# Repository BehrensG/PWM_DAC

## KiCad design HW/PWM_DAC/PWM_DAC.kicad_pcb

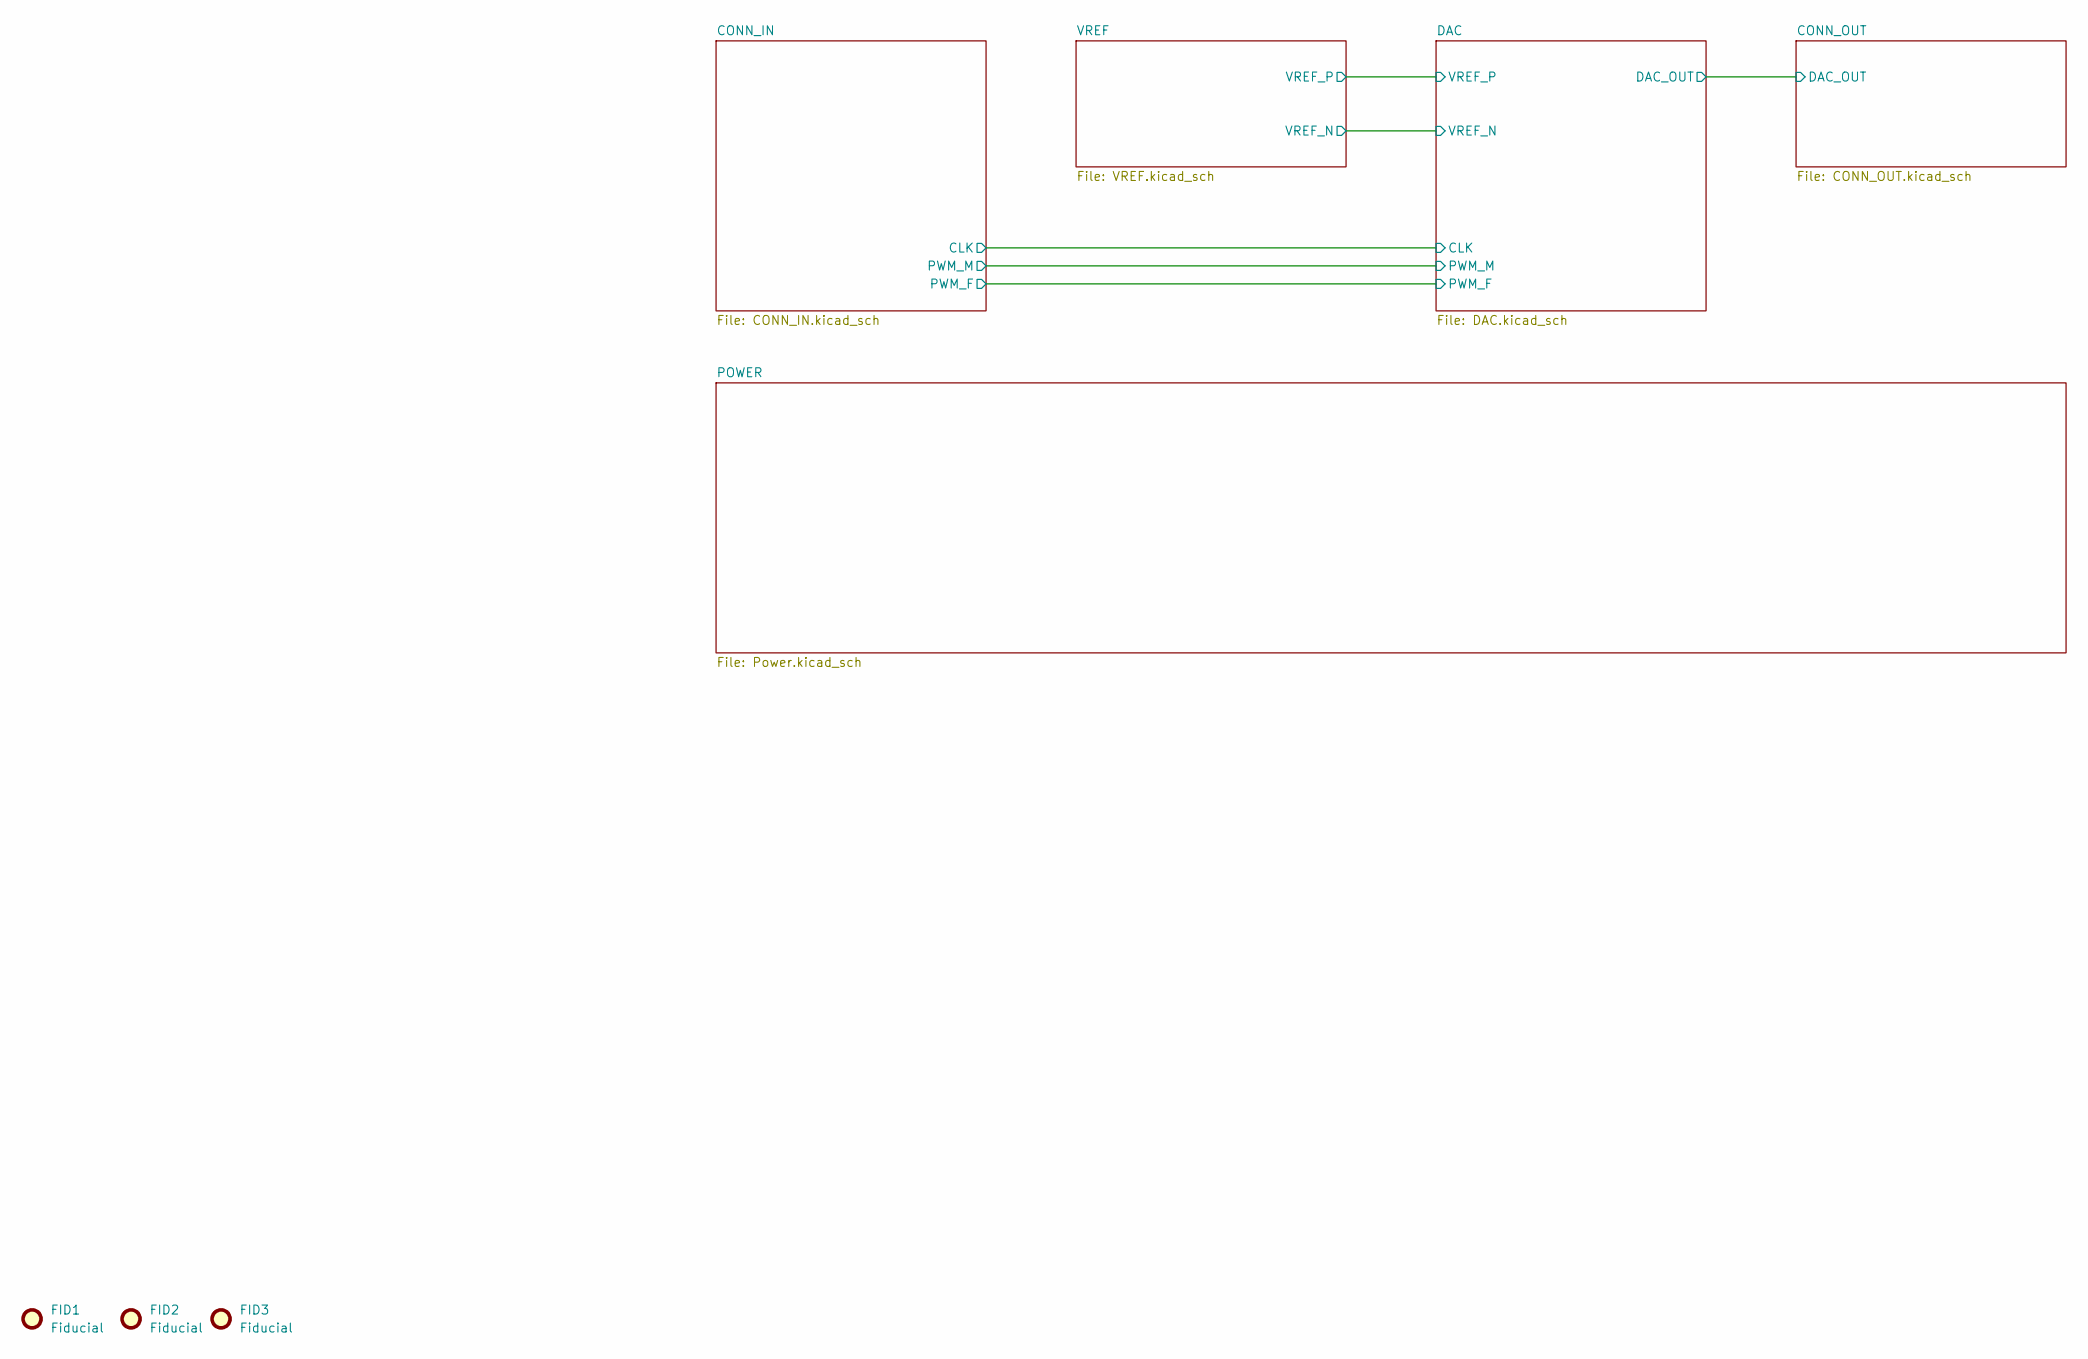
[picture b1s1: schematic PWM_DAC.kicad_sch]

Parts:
FID1, FID2, FID3: Fiducial; Fiducial_1.5mm_Mask3mm

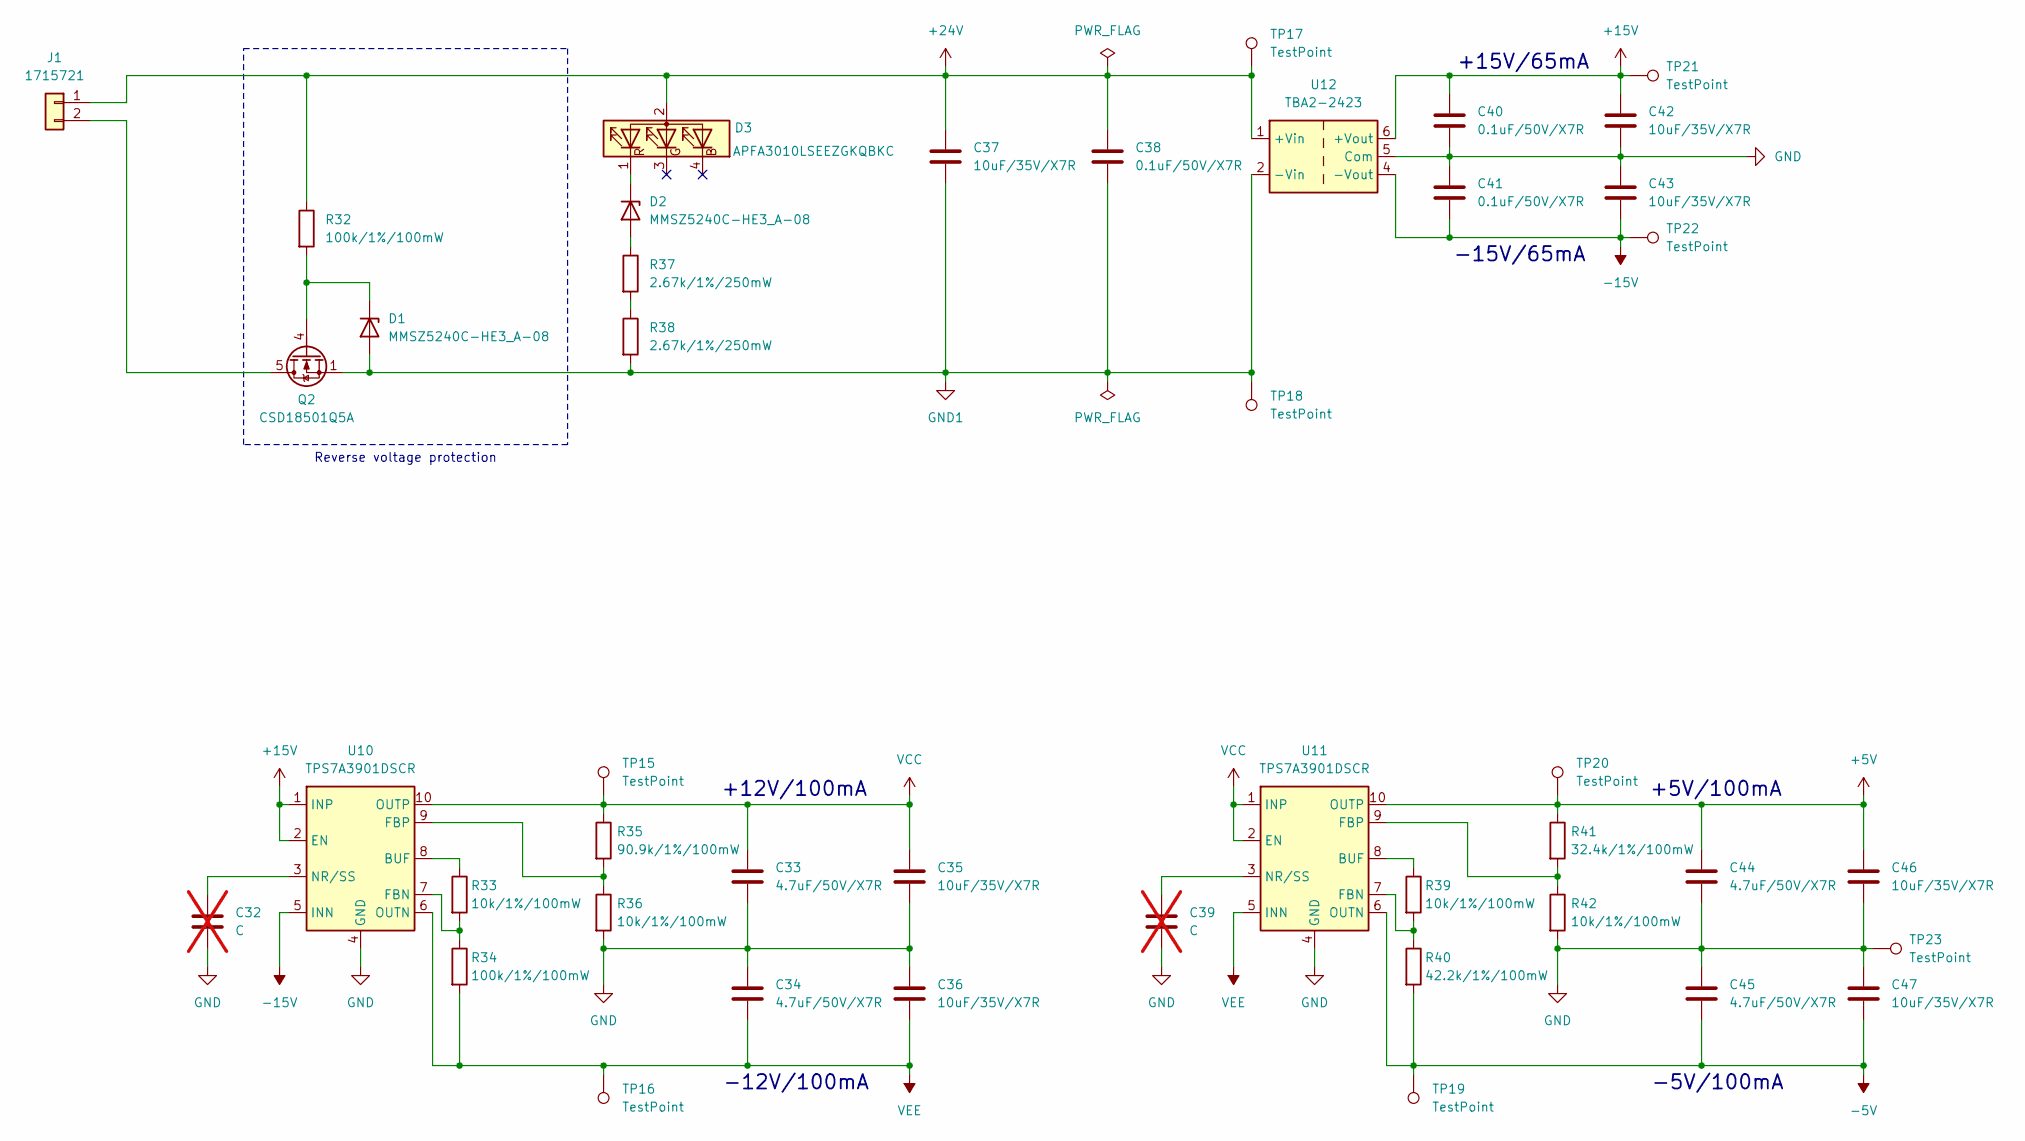
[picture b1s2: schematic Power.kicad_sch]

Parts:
C32, C39: C; C_0603_1608Metric_Pad1.08x0.95mm_HandSolder; not fitted
C33, C34, C44, C45: 4.7uF/50V/X7R; C_1206_3216Metric_Pad1.33x1.80mm_HandSolder
C35, C36, C37, C42, C43, C46, C47: 10uF/35V/X7R; C_1206_3216Metric_Pad1.33x1.80mm_HandSolder
C38, C40, C41: 0.1uF/50V/X7R; C_0603_1608Metric_Pad1.08x0.95mm_HandSolder
D1, D2: MMSZ5240C-HE3_A-08; D_SOD-123
D3: APFA3010LSEEZGKQBKC; LED_Kingbright_APFA3010_3x1.5mm_Horizontal
J1: 1715721; TerminalBlock_Phoenix_MKDS-1,5-2_1x02_P5.00mm_Horizontal
Q2: CSD18501Q5A; TDSON-8-1
R32, R34: 100k/1%/100mW; R_0603_1608Metric_Pad0.98x0.95mm_HandSolder
R33, R36, R39, R42: 10k/1%/100mW; R_0603_1608Metric_Pad0.98x0.95mm_HandSolder
R35: 90.9k/1%/100mW; R_0603_1608Metric_Pad0.98x0.95mm_HandSolder
R37, R38: 2.67k/1%/250mW; R_0805_2012Metric_Pad1.20x1.40mm_HandSolder
R40: 42.2k/1%/100mW; R_0603_1608Metric_Pad0.98x0.95mm_HandSolder
R41: 32.4k/1%/100mW; R_0603_1608Metric_Pad0.98x0.95mm_HandSolder
TP15, TP16, TP17, TP18, TP19, TP20, TP21, TP22, TP23: TestPoint; TestPoint_Pad_D1.5mm
U10, U11: TPS7A3901DSCR; Texas_S-PVSON-N10_ThermalVias
U12: TBA2-2423; Converter_DCDC_TRACO_TBA2-xxxx_Dual_THT

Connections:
+5V: C44.1, C46.1, R41.1, TP20.1 (1_1), U11.10 (OUTP); also elsewhere on the board
+15V: C40.2, C42.2, TP21.1 (1_1), U10.1 (INP), U10.2 (EN), U12.6 (+Vout)
+24V: C37.2, C38.2, D3.2 (A), J1.1, R32.1, TP17.1 (1_1), U12.1 (+Vin)
-5V: C45.2, C47.2, R40.2, TP19.1 (1_1), U11.6 (OUTN); also elsewhere on the board
-15V: C41.1, C43.1, TP22.1 (1_1), U10.5 (INN), U12.4 (-Vout)
GND: C32.2, C33.2, C34.1, C35.2, C36.1, C39.2, C40.1, C41.2, C42.1, C43.2, C44.2, C45.1, C46.2, C47.1, R36.2, R42.2, TP23.1 (1_1), U10.4 (GND), U10.11 (GND), U11.4 (GND), U11.11 (GND), U12.5 (Com); also elsewhere on the board
GND1: C37.1, C38.1, D1.2 (A), Q2.1 (S), Q2.2 (S), Q2.3 (S), R38.2, TP18.1 (1_1), U12.2 (-Vin)
unnamed: D1.1 (K), Q2.4 (G), R32.2
unnamed: D2.2 (A), R37.1
unnamed: D2.1 (K), D3.1 (R)
unnamed: J1.2, Q2.5 (D)
unnamed: R37.2, R38.1
unnamed: R33.1, U10.8 (BUF)
unnamed: R33.2, R34.1, U10.7 (FBN)
unnamed: R35.2, R36.1, U10.9 (FBP)
unnamed: C32.1, U10.3 (NR/SS)
unnamed: R39.1, U11.8 (BUF)
unnamed: R39.2, R40.1, U11.7 (FBN)
unnamed: R41.2, R42.1, U11.9 (FBP)
unnamed: C39.1, U11.3 (NR/SS)
VCC: C33.1, C35.1, R35.1, TP15.1 (1_1), U10.10 (OUTP), U11.1 (INP), U11.2 (EN); also elsewhere on the board
VEE: C34.2, C36.2, R34.2, TP16.1 (1_1), U10.6 (OUTN), U11.5 (INN); also elsewhere on the board

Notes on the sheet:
-5V/100mA
-12V/100mA
+12V/100mA
+5V/100mA
-15V/65mA
+15V/65mA
Reverse voltage protection

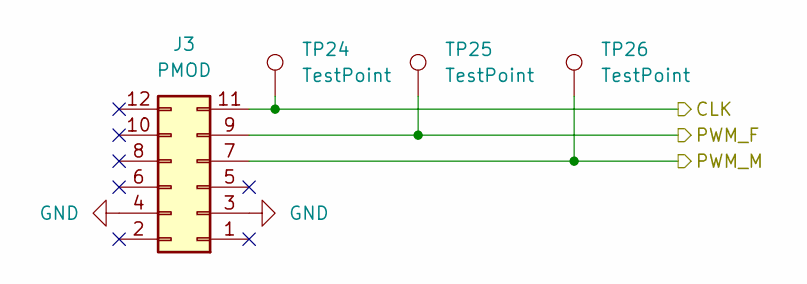
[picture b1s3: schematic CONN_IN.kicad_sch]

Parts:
J3: PMOD; PinHeader_2x06_P2.54mm_Horizontal
TP24, TP25, TP26: TestPoint; TestPoint_Pad_D1.5mm

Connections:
/CONN_IN/PWM_F: J3.9, TP25.1 (1_1); also elsewhere on the board
/CONN_IN/PWM_M: J3.7, TP26.1 (1_1); also elsewhere on the board
/DAC/CLK: J3.11, TP24.1 (1_1); also elsewhere on the board
GND: J3.3, J3.4; also elsewhere on the board

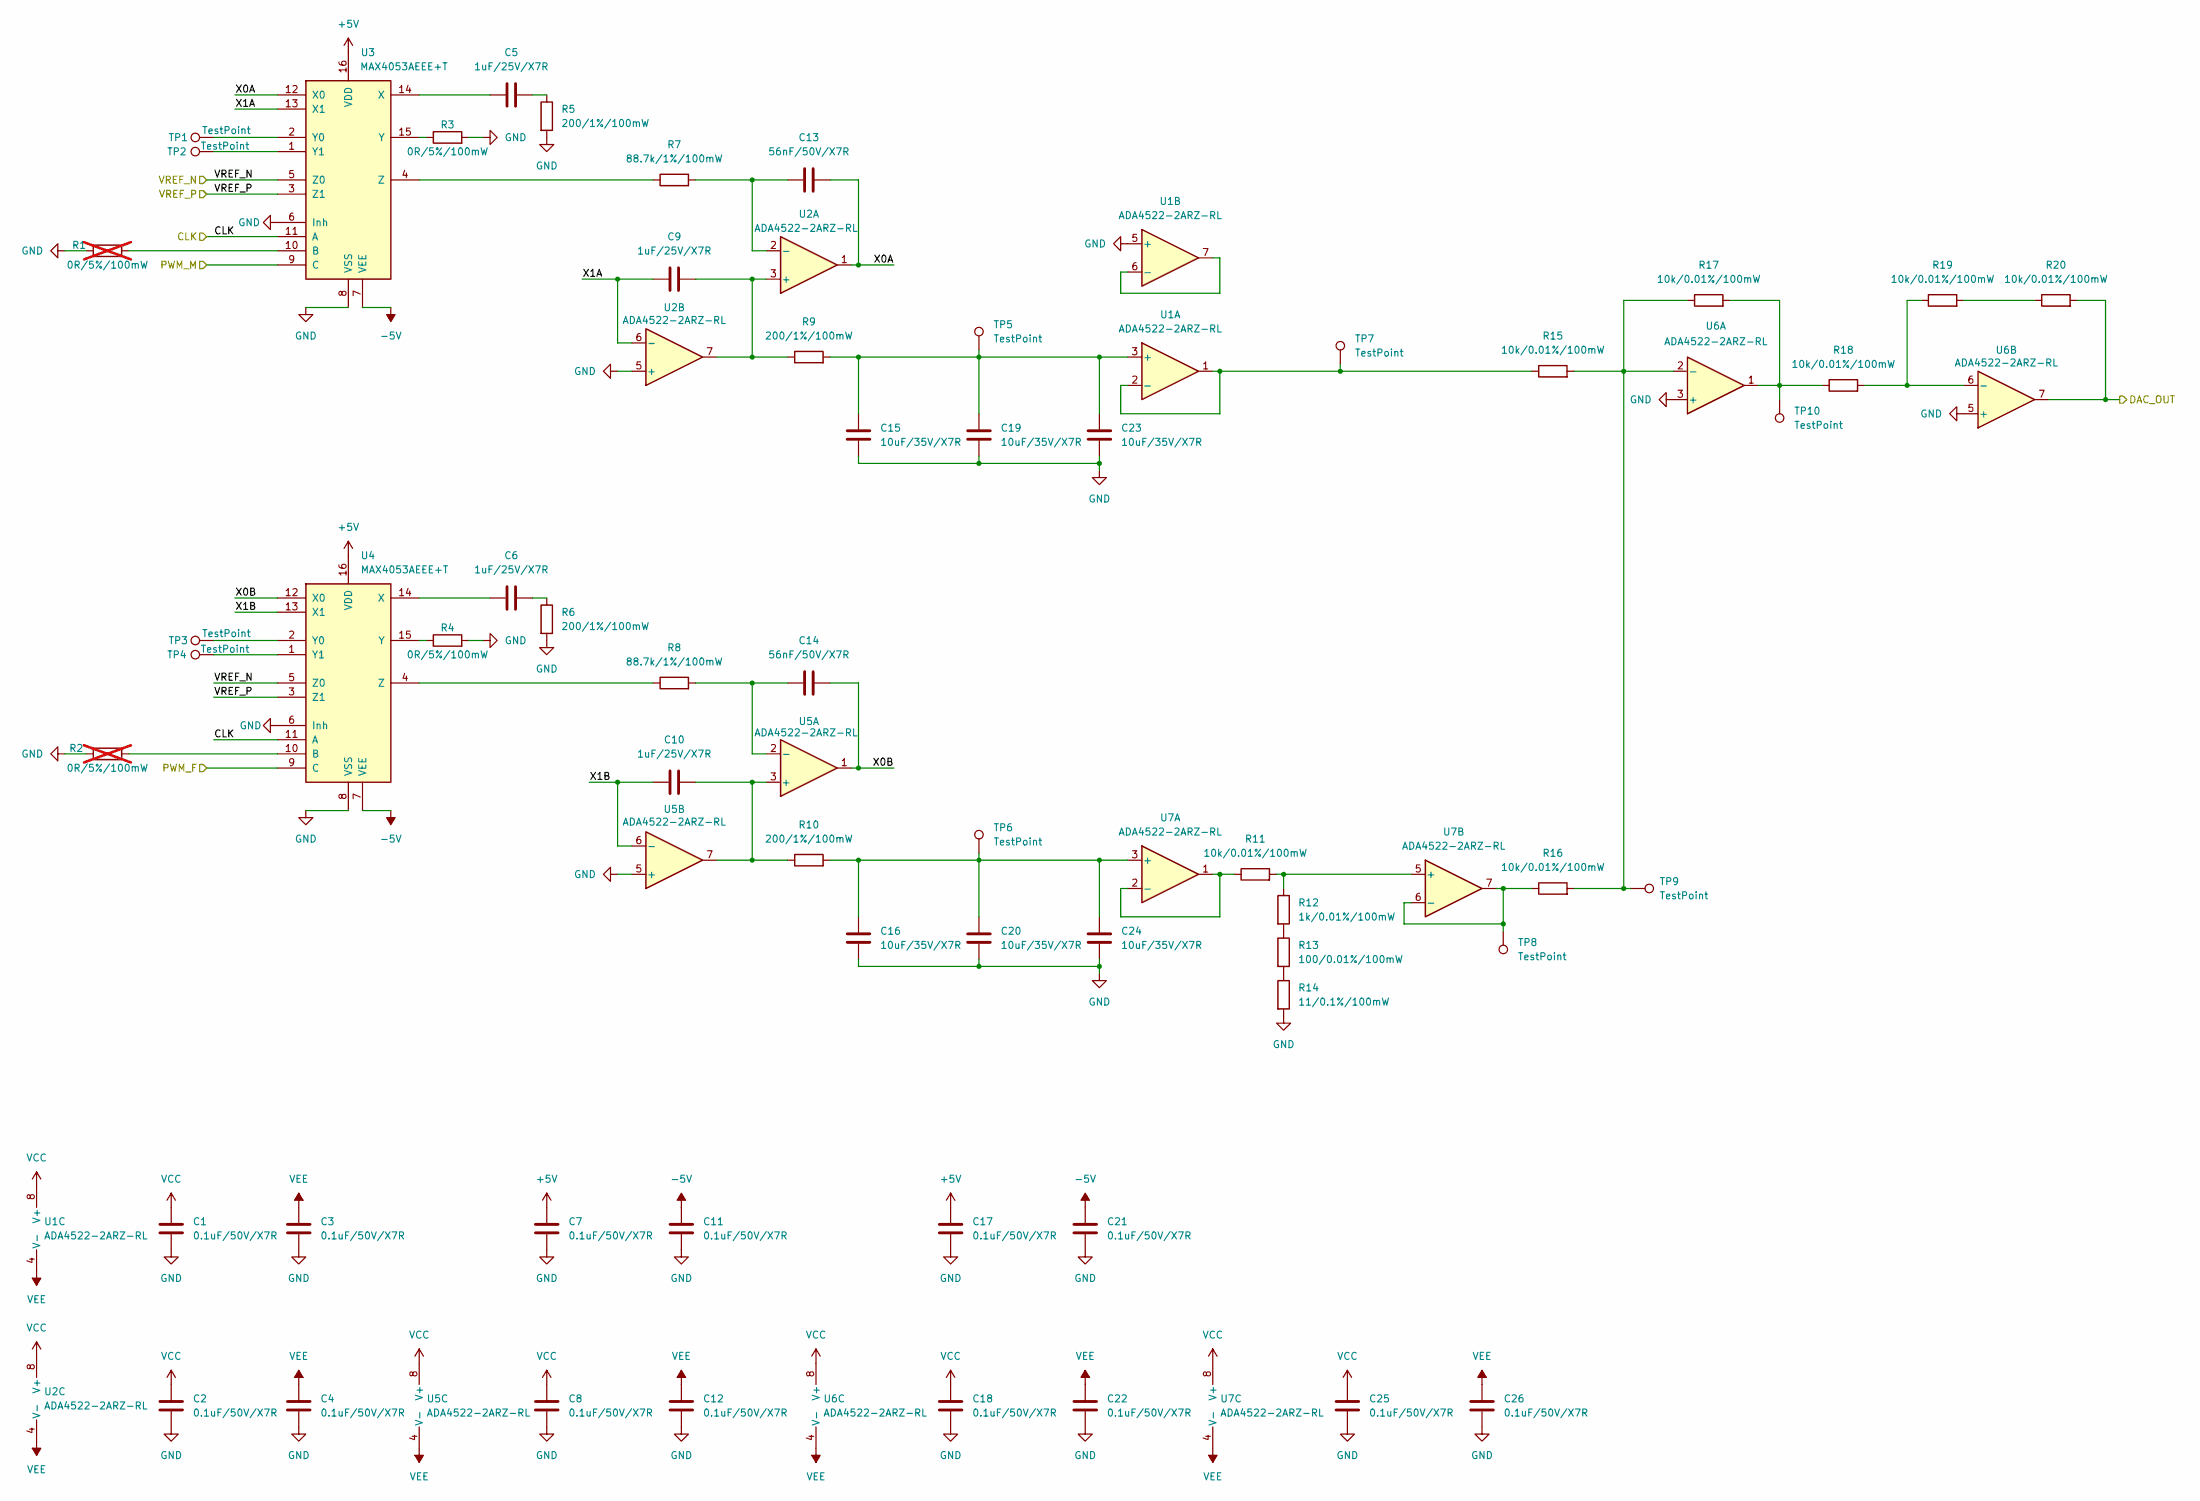
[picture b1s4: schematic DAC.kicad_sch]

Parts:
C1, C2, C3, C4, C7, C8, C11, C12, C17, C18, C21, C22, C25, C26: 0.1uF/50V/X7R; C_0603_1608Metric_Pad1.08x0.95mm_HandSolder
C5, C6, C9, C10: 1uF/25V/X7R; C_0603_1608Metric_Pad1.08x0.95mm_HandSolder
C13, C14: 56nF/50V/X7R; C_0603_1608Metric_Pad1.08x0.95mm_HandSolder
C15, C16, C19, C20, C23, C24: 10uF/35V/X7R; C_1206_3216Metric_Pad1.33x1.80mm_HandSolder
R1, R2: 0R/5%/100mW; R_0603_1608Metric_Pad0.98x0.95mm_HandSolder; not fitted
R3, R4: 0R/5%/100mW; R_0603_1608Metric_Pad0.98x0.95mm_HandSolder
R5, R6, R9, R10: 200/1%/100mW; R_0603_1608Metric_Pad0.98x0.95mm_HandSolder
R7, R8: 88.7k/1%/100mW; R_0603_1608Metric_Pad0.98x0.95mm_HandSolder
R11, R15, R16, R17, R18, R19, R20: 10k/0.01%/100mW; R_0805_2012Metric_Pad1.20x1.40mm_HandSolder
R12: 1k/0.01%/100mW; R_0805_2012Metric_Pad1.20x1.40mm_HandSolder
R13: 100/0.01%/100mW; R_0805_2012Metric_Pad1.20x1.40mm_HandSolder
R14: 11/0.1%/100mW; R_0805_2012Metric_Pad1.20x1.40mm_HandSolder
TP1, TP2, TP3, TP4, TP5, TP6, TP7, TP8, TP9, TP10: TestPoint; TestPoint_Pad_D1.5mm
U1, U2, U5, U6, U7: ADA4522-2ARZ-RL; SOIC-8_3.9x4.9mm_P1.27mm
U3, U4: MAX4053AEEE+T; QSOP-16_3.9x4.9mm_P0.635mm

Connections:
+5V: C7.2, C17.2, U3.16 (VDD), U4.16 (VDD); also elsewhere on the board
-5V: C11.2, C21.2, U3.7 (VEE), U4.7 (VEE); also elsewhere on the board
/CONN_IN/PWM_F: U4.9 (C); also elsewhere on the board
/CONN_IN/PWM_M: U3.9 (C); also elsewhere on the board
/CONN_OUT/DAC_OUT: R20.2, U6.7; also elsewhere on the board
/DAC/CLK: U3.11 (A), U4.11 (A); also elsewhere on the board
/DAC/VREF_N: U3.5 (Z0), U4.5 (Z0); also elsewhere on the board
/DAC/VREF_P: U3.3 (Z1), U4.3 (Z1); also elsewhere on the board
/DAC/X0A: C13.2, U2.1, U3.12 (X0)
/DAC/X0B: C14.2, U4.12 (X0), U5.1
/DAC/X1A: C9.1, U2.6 (-), U3.13 (X1)
/DAC/X1B: C10.1, U4.13 (X1), U5.6 (-)
GND: C1.1, C2.1, C3.1, C4.1, C7.1, C8.1, C11.1, C12.1, C15.1, C16.1, C17.1, C18.1, C19.1, C20.1, C21.1, C22.1, C23.1, C24.1, C25.1, C26.1, R1.1, R2.1, R3.2, R4.2, R5.2, R6.2, R14.2, U1.5 (+), U2.5 (+), U3.6 (Inh), U3.8 (VSS), U4.6 (Inh), U4.8 (VSS), U5.5 (+), U6.3 (+), U6.5 (+); also elsewhere on the board
unnamed: C5.2, R5.1
unnamed: C6.2, R6.1
unnamed: R12.2, R13.1
unnamed: R13.2, R14.1
unnamed: R17.2, R18.1, TP10.1 (1_1), U6.1
unnamed: R19.2, R20.1
unnamed: C15.2, C19.2, C23.2, R9.2, TP5.1 (1_1), U1.3 (+)
unnamed: R15.1, TP7.1 (1_1), U1.1, U1.2 (-)
unnamed: U1.6 (-), U1.7
unnamed: C9.2, R9.1, U2.3 (+), U2.7
unnamed: C13.1, R7.2, U2.2 (-)
unnamed: R1.2, U3.10 (B)
unnamed: C5.1, U3.14 (X)
unnamed: TP1.1 (1_1), U3.2 (Y0)
unnamed: TP2.1 (1_1), U3.1 (Y1)
unnamed: R3.1, U3.15 (Y)
unnamed: R7.1, U3.4 (Z)
unnamed: R2.2, U4.10 (B)
unnamed: C6.1, U4.14 (X)
unnamed: TP3.1 (1_1), U4.2 (Y0)
unnamed: TP4.1 (1_1), U4.1 (Y1)
unnamed: R4.1, U4.15 (Y)
unnamed: R8.1, U4.4 (Z)
unnamed: C10.2, R10.1, U5.3 (+), U5.7
unnamed: C14.1, R8.2, U5.2 (-)
unnamed: R15.2, R16.2, R17.1, TP9.1 (1_1), U6.2 (-)
unnamed: R18.2, R19.1, U6.6 (-)
unnamed: C16.2, C20.2, C24.2, R10.2, TP6.1 (1_1), U7.3 (+)
unnamed: R11.1, U7.1, U7.2 (-)
unnamed: R11.2, R12.1, U7.5 (+)
unnamed: R16.1, TP8.1 (1_1), U7.6 (-), U7.7
VCC: C1.2, C2.2, C8.2, C18.2, C25.2, U1.8 (V+), U2.8 (V+), U5.8 (V+), U6.8 (V+), U7.8 (V+); also elsewhere on the board
VEE: C3.2, C4.2, C12.2, C22.2, C26.2, U1.4 (V-), U2.4 (V-), U5.4 (V-), U6.4 (V-), U7.4 (V-); also elsewhere on the board

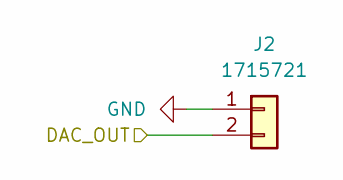
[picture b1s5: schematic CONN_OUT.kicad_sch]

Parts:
J2: 1715721; TerminalBlock_Phoenix_MKDS-1,5-2_1x02_P5.00mm_Horizontal

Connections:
/CONN_OUT/DAC_OUT: J2.2; also elsewhere on the board
GND: J2.1; also elsewhere on the board

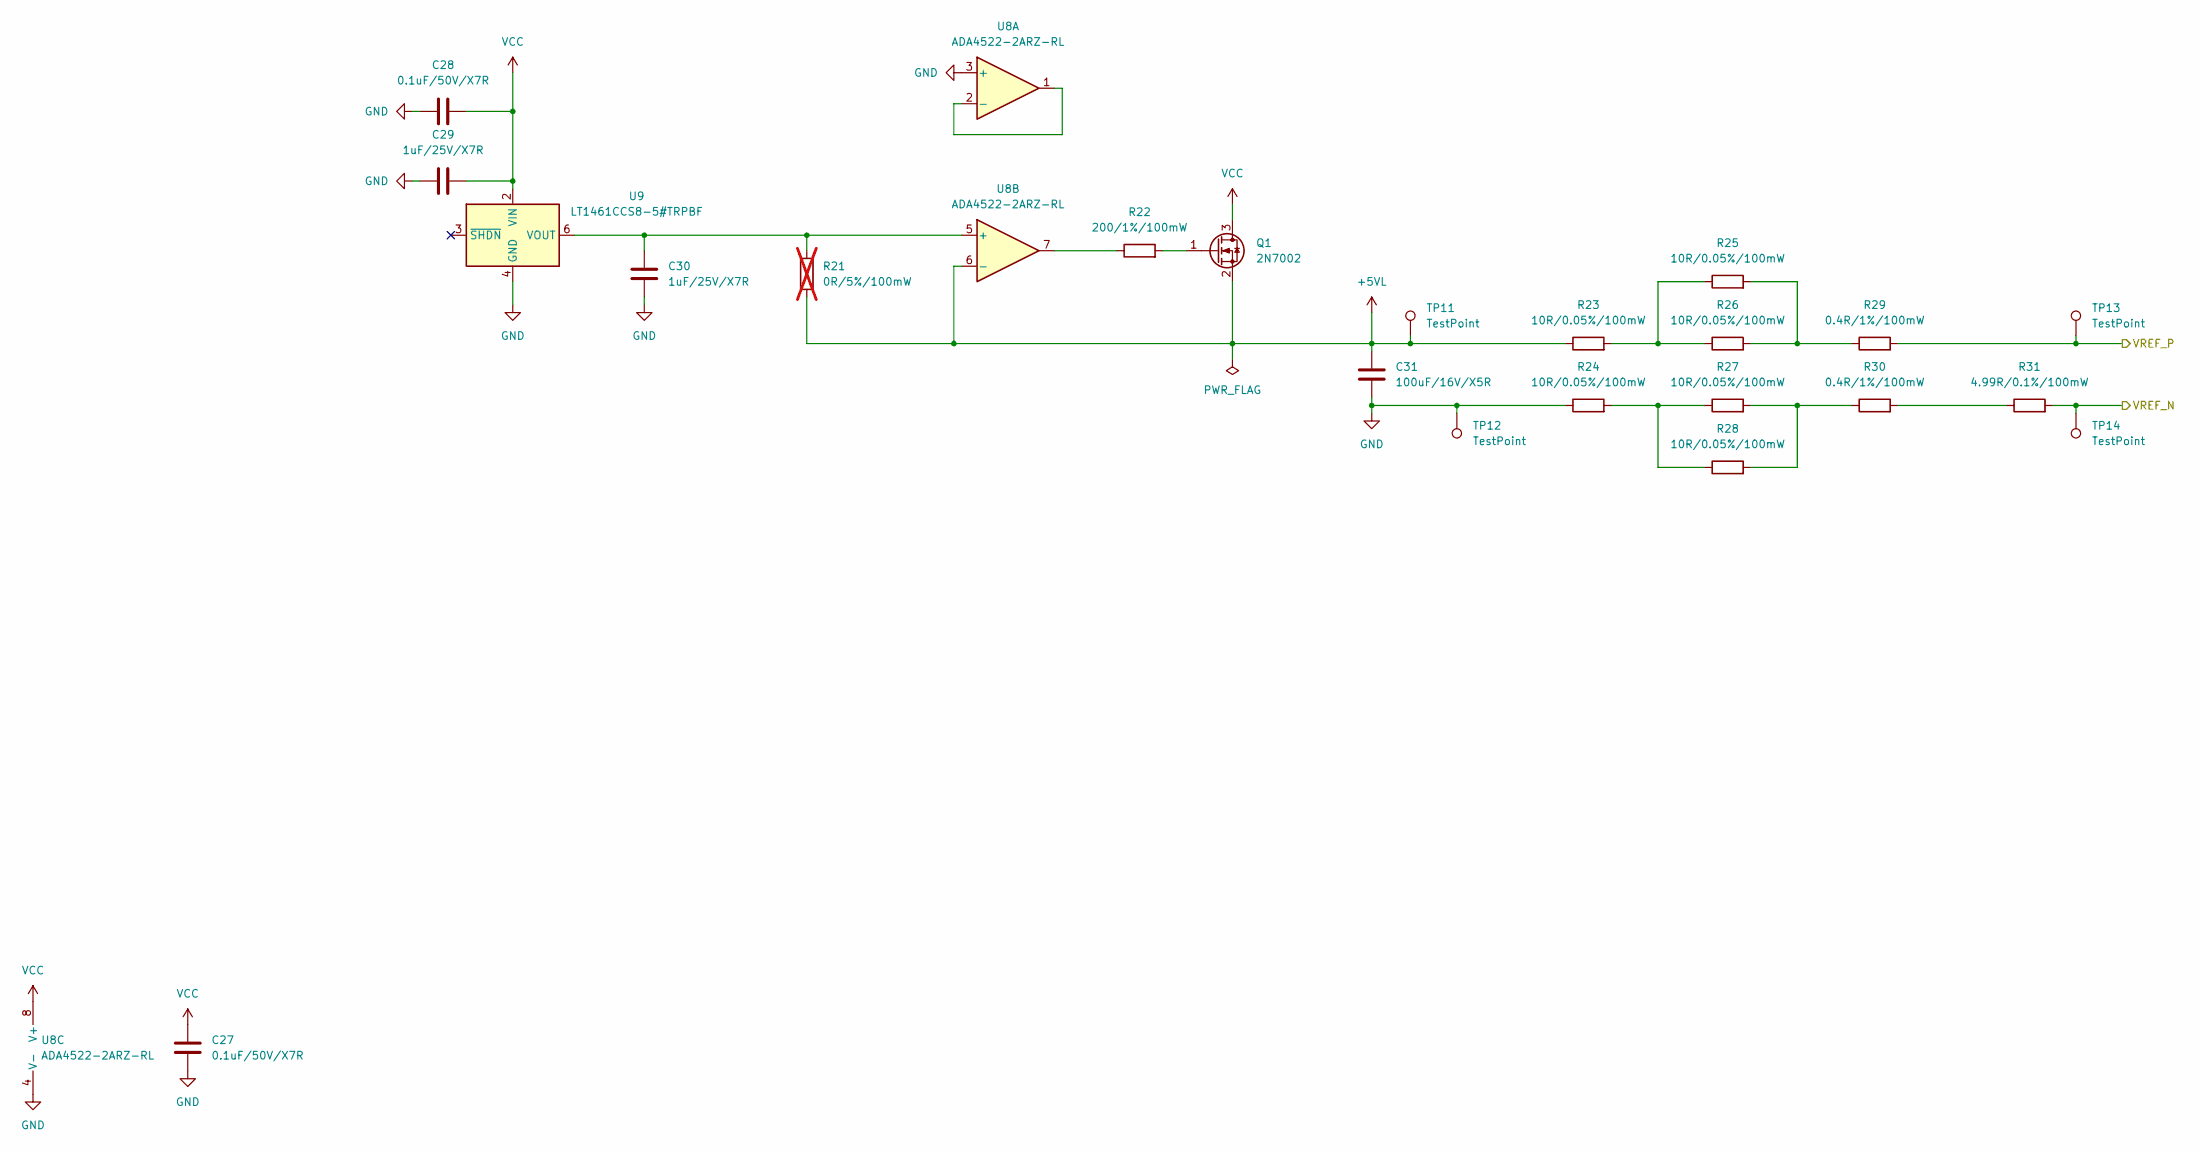
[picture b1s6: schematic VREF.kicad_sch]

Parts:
C27, C28: 0.1uF/50V/X7R; C_0603_1608Metric_Pad1.08x0.95mm_HandSolder
C29, C30: 1uF/25V/X7R; C_0603_1608Metric_Pad1.08x0.95mm_HandSolder
C31: 100uF/16V/X5R; C_1210_3225Metric_Pad1.33x2.70mm_HandSolder
Q1: 2N7002; SOT-23
R21: 0R/5%/100mW; R_0603_1608Metric_Pad0.98x0.95mm_HandSolder; not fitted
R22: 200/1%/100mW; R_0603_1608Metric_Pad0.98x0.95mm_HandSolder
R23, R24, R25, R26, R27, R28: 10R/0.05%/100mW; R_0805_2012Metric_Pad1.20x1.40mm_HandSolder
R29, R30: 0.4R/1%/100mW; R_0603_1608Metric_Pad0.98x0.95mm_HandSolder
R31: 4.99R/0.1%/100mW; R_0805_2012Metric_Pad1.20x1.40mm_HandSolder
TP11, TP12, TP13, TP14: TestPoint; TestPoint_Pad_D1.5mm
U8: ADA4522-2ARZ-RL; SOIC-8_3.9x4.9mm_P1.27mm
U9: LT1461CCS8-5#TRPBF; SOIC-8_3.9x4.9mm_P1.27mm

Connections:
+5VL: C31.1, Q1.2 (S), R21.2, R23.1, TP11.1 (1_1), U8.6 (-)
/DAC/VREF_N: R31.2, TP14.1 (1_1); also elsewhere on the board
/DAC/VREF_P: R29.2, TP13.1 (1_1); also elsewhere on the board
GND: C27.1, C28.1, C29.1, C30.2, C31.2, R24.1, TP12.1 (1_1), U8.3 (+), U8.4 (V-), U9.4 (GND); also elsewhere on the board
unnamed: Q1.1 (G), R22.2
unnamed: R22.1, U8.7
unnamed: R23.2, R25.1, R26.1
unnamed: R24.2, R27.1, R28.1
unnamed: R25.2, R26.2, R29.1
unnamed: R27.2, R28.2, R30.1
unnamed: R30.2, R31.1
unnamed: U8.1, U8.2 (-)
unnamed: C30.1, R21.1, U8.5 (+), U9.6 (VOUT)
VCC: C27.2, C28.2, C29.2, Q1.3 (D), U8.8 (V+), U9.2 (VIN); also elsewhere on the board

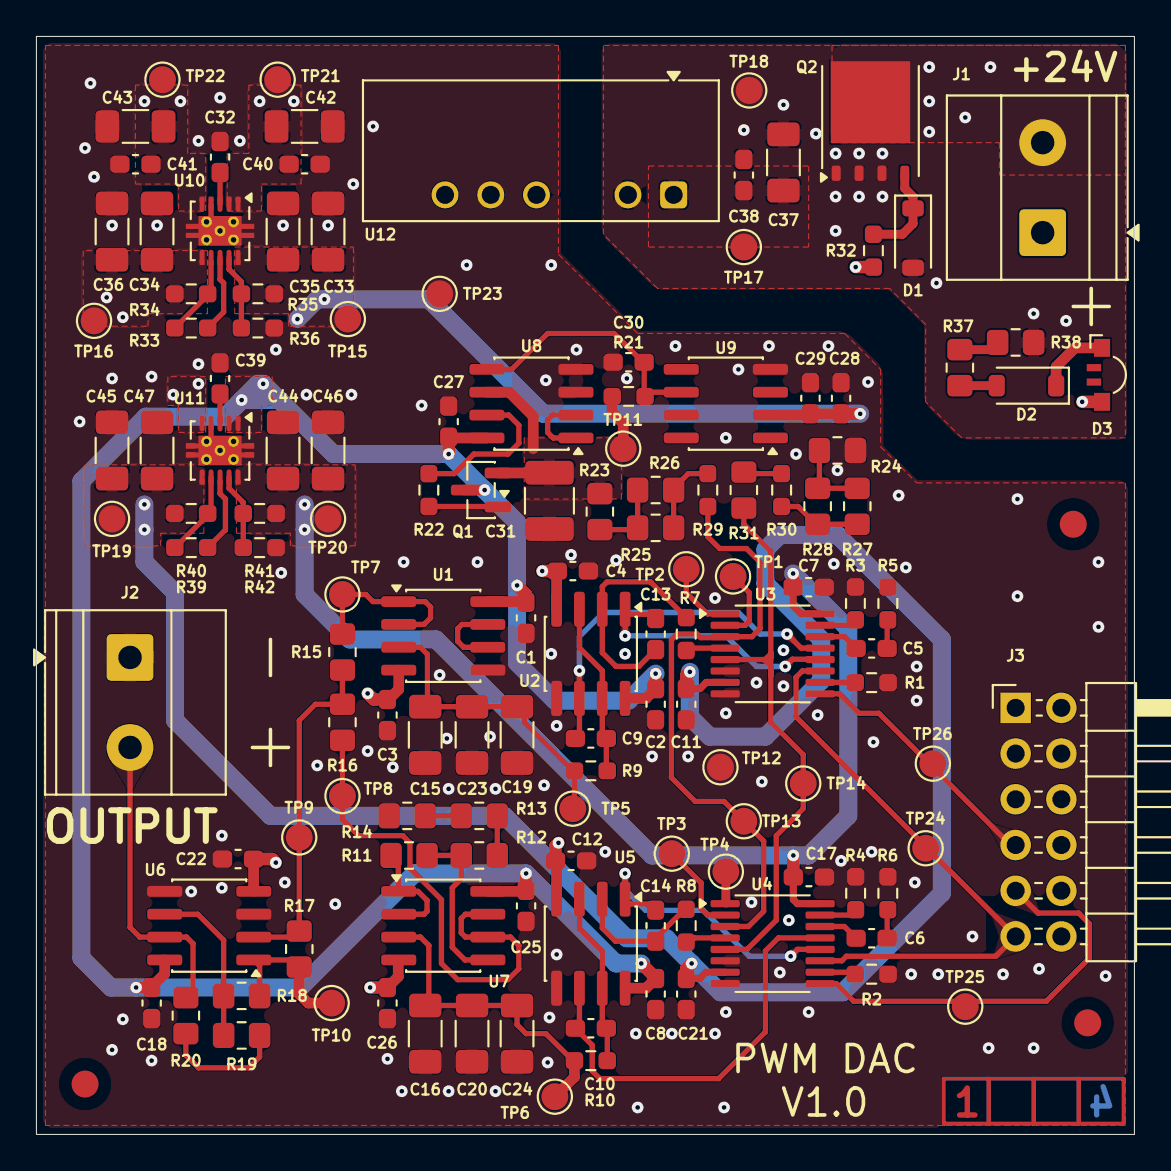
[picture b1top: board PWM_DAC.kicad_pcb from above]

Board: 4 copper layers, 61.0 x 61.0 mm, 138 parts (0 on the bottom side), 73 nets.

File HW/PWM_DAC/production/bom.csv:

Designator,Footprint,Quantity,Value,LCSC Part #
"C1, C11, C12, C17, C18, C2, C21, C22, C25, C26, C27, C28, C3, C38, C4, C40, C41, C7, C8",0603,19,0.1uF/50V/X7R,
"C10, C29, C30, C5, C6, C9",0603,6,1uF/25V/X7R,
"C13, C14",0603,2,56nF/50V/X7R,
"C15, C16, C19, C20, C23, C24, C35, C36, C37, C42, C43, C46, C47",1206,13,10uF/35V/X7R,
C31,1210,1,100uF/16V/X5R,
"C33, C34, C44, C45",1206,4,4.7uF/50V/X7R,
"D1, D2",D_SOD-123,2,MMSZ5240C-HE3_A-08,
D3,LED_Kingbright_APFA3010_3x1.5mm_Horizontal,1,APFA3010LSEEZGKQBKC,
"J1, J2","TerminalBlock_Phoenix_MKDS-1,5-2_1x02_P5.00mm_Horizontal",2,1715721,
J3,PinHeader_2x06_P2.54mm_Horizontal,1,PMOD,
Q1,SOT-23,1,2N7002,
Q2,TDSON-8-1,1,CSD18501Q5A,
"R1, R2, R3, R4",0603,4,0R/5%/100mW,
"R10, R22, R5, R6, R9",0603,5,200/1%/100mW,
"R11, R15, R16, R17, R18, R19, R20",0805,7,10k/0.01%/100mW,
R12,0805,1,1k/0.01%/100mW,
R13,0805,1,100/0.01%/100mW,
R14,0805,1,11/0.1%/100mW,
"R23, R24, R25, R26, R27, R28",0805,6,10R/0.05%/100mW,
"R29, R30",0603,2,0.4R/1%/100mW,
R31,0805,1,4.99R/0.1%/100mW,
"R32, R34",0603,2,100k/1%/100mW,
"R33, R36, R39, R42",0603,4,10k/1%/100mW,
R35,0603,1,90.9k/1%/100mW,
"R37, R38",0805,2,2.67k/1%/250mW,
R40,0603,1,42.2k/1%/100mW,
R41,0603,1,32.4k/1%/100mW,
"R7, R8",0603,2,88.7k/1%/100mW,
"U1, U2, U5, U6, U7, U8",SOIC-8_3.9x4.9mm_P1.27mm,6,ADA4522-2ARZ-RL,
"U10, U11",Texas_S-PVSON-N10_ThermalVias,2,TPS7A3901DSCR,
U12,Converter_DCDC_TRACO_TBA2-xxxx_Dual_THT,1,TBA2-2423,
"U3, U4",QSOP-16_3.9x4.9mm_P0.635mm,2,MAX4053AEEE+T,
U9,SOIC-8_3.9x4.9mm_P1.27mm,1,ADR4550BRZ-R7,
